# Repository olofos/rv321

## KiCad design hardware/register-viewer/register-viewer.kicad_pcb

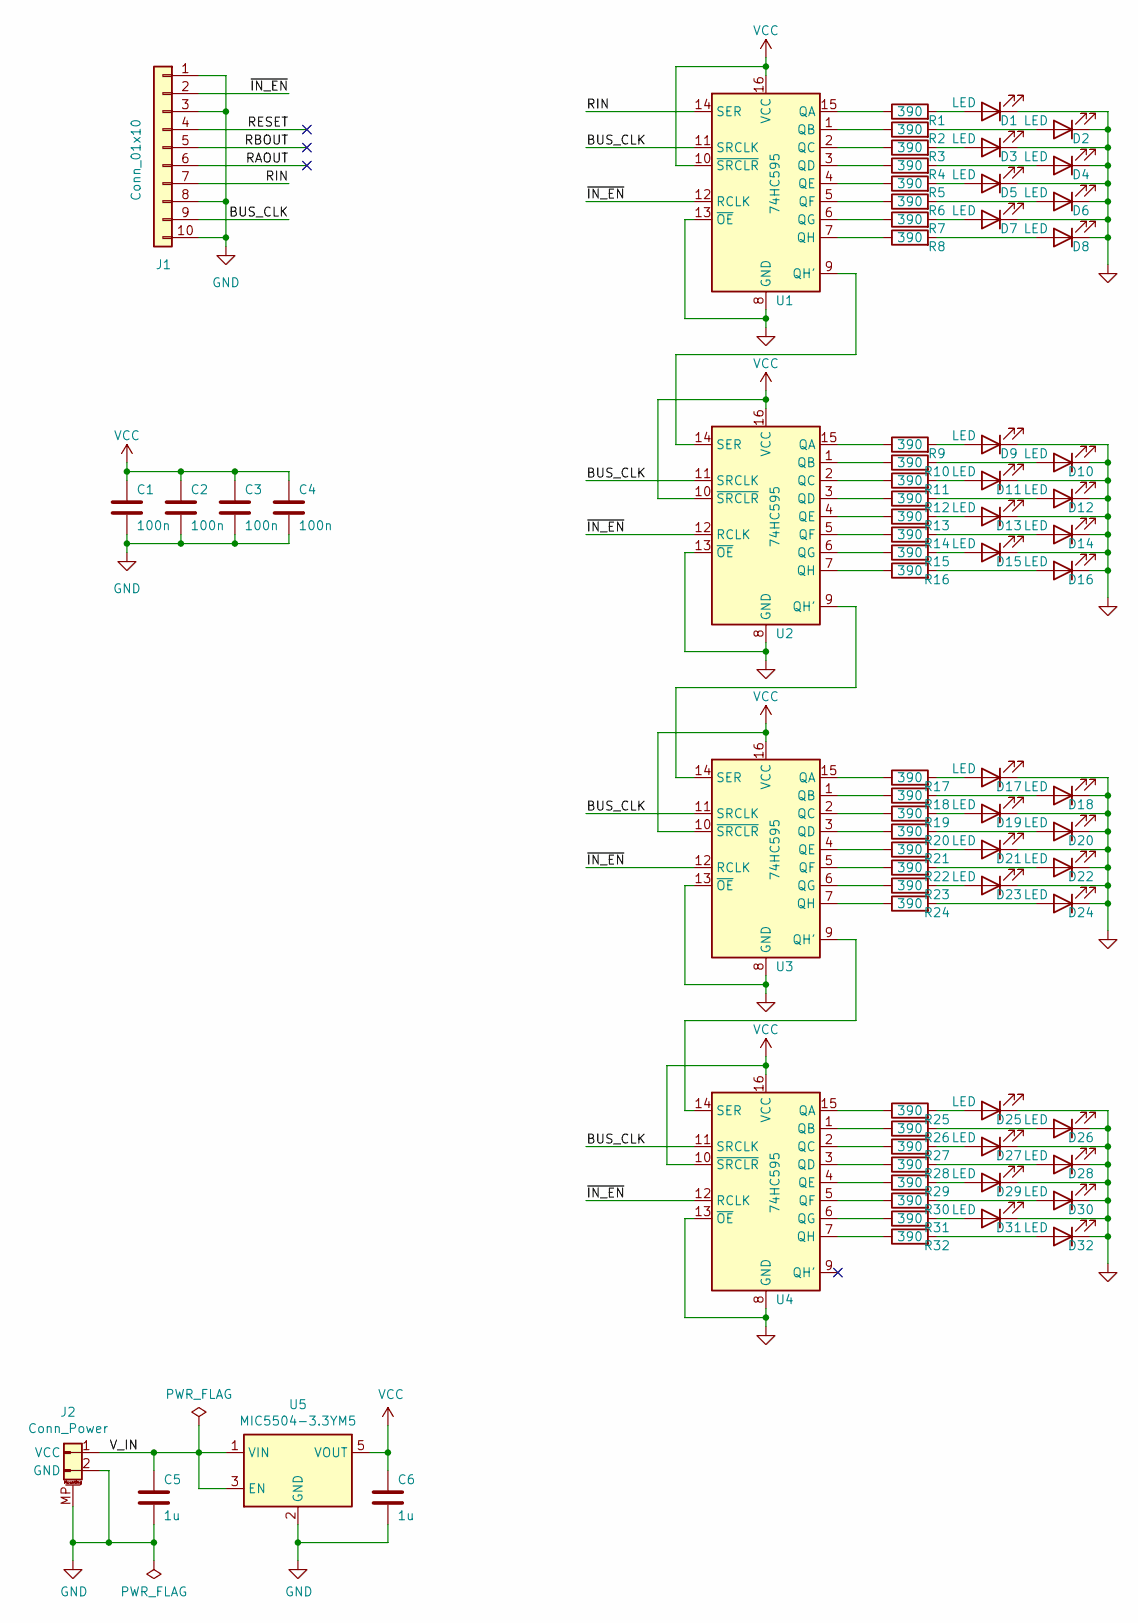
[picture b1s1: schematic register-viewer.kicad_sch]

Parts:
C1, C2, C3, C4: 100n; C_0805_2012Metric_Pad1.18x1.45mm_HandSolder
C5, C6: 1u; C_0805_2012Metric_Pad1.18x1.45mm_HandSolder
D1, D2, D3, D4, D5, D6, D7, D8, D9, D10, D11, D12, D13, D14, D15, D16, D17, D18, D19, D20, D21, D22, D23, D24, D25, D26, D27, D28, D29, D30, D31, D32: LED; LED_0805_2012Metric_Pad1.15x1.40mm_HandSolder
J1: Conn_01x10; IDC-Header_2x05_P2.54mm_Vertical
J2: Conn_Power; JST_PH_S2B-PH-SM4-TB_1x02-1MP_P2.00mm_Horizontal
R1, R2, R3, R4, R5, R6, R7, R8, R9, R10, R11, R12, R13, R14, R15, R16, R17, R18, R19, R20, R21, R22, R23, R24, R25, R26, R27, R28, R29, R30, R31, R32: 390; R_0805_2012Metric_Pad1.20x1.40mm_HandSolder
U1, U2, U3, U4: 74HC595; SOIC-16_3.9x9.9mm_P1.27mm
U5: MIC5504-3.3YM5; SOT-23-5_HandSoldering

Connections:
/BUS_CLK: J1.9, U1.11 (SRCLK), U2.11 (SRCLK), U3.11 (SRCLK), U4.11 (SRCLK)
/RAOUT: J1.6
/RBOUT: J1.5
/RESET: J1.4
/RIN: J1.7, U1.14 (SER)
/V_IN: C5.1, J2.1 (VCC), U5.1 (VIN), U5.3 (EN)
/~IN_EN: J1.2, U1.12 (RCLK), U2.12 (RCLK), U3.12 (RCLK), U4.12 (RCLK)
GND: C1.2, C2.2, C3.2, C4.2, C5.2, C6.2, D1.1 (K), D2.1 (K), D3.1 (K), D4.1 (K), D5.1 (K), D6.1 (K), D7.1 (K), D8.1 (K), D9.1 (K), D10.1 (K), D11.1 (K), D12.1 (K), D13.1 (K), D14.1 (K), D15.1 (K), D16.1 (K), D17.1 (K), D18.1 (K), D19.1 (K), D20.1 (K), D21.1 (K), D22.1 (K), D23.1 (K), D24.1 (K), D25.1 (K), D26.1 (K), D27.1 (K), D28.1 (K), D29.1 (K), D30.1 (K), D31.1 (K), D32.1 (K), J1.1, J1.3, J1.8, J1.10, J2.2 (GND), J2.MP, U1.8 (GND), U1.13 (~OE), U2.8 (GND), U2.13 (~OE), U3.8 (GND), U3.13 (~OE), U4.8 (GND), U4.13 (~OE), U5.2 (GND)
unnamed: D1.2 (A), R1.2
unnamed: D2.2 (A), R2.2
unnamed: D3.2 (A), R3.2
unnamed: D4.2 (A), R4.2
unnamed: D5.2 (A), R5.2
unnamed: D6.2 (A), R6.2
unnamed: D7.2 (A), R7.2
unnamed: D8.2 (A), R8.2
unnamed: D9.2 (A), R9.2
unnamed: D10.2 (A), R10.2
unnamed: D11.2 (A), R11.2
unnamed: D12.2 (A), R12.2
unnamed: D13.2 (A), R13.2
unnamed: D14.2 (A), R14.2
unnamed: D15.2 (A), R15.2
unnamed: D16.2 (A), R16.2
unnamed: D17.2 (A), R17.2
unnamed: D18.2 (A), R18.2
unnamed: D19.2 (A), R19.2
unnamed: D20.2 (A), R20.2
unnamed: D21.2 (A), R21.2
unnamed: D22.2 (A), R22.2
unnamed: D23.2 (A), R23.2
unnamed: D24.2 (A), R24.2
unnamed: D25.2 (A), R25.2
unnamed: D26.2 (A), R26.2
unnamed: D27.2 (A), R27.2
unnamed: D28.2 (A), R28.2
unnamed: D29.2 (A), R29.2
unnamed: D30.2 (A), R30.2
unnamed: D31.2 (A), R31.2
unnamed: D32.2 (A), R32.2
unnamed: R1.1, U1.15 (QA)
unnamed: R2.1, U1.1 (QB)
unnamed: R3.1, U1.2 (QC)
unnamed: R4.1, U1.3 (QD)
unnamed: R5.1, U1.4 (QE)
unnamed: R6.1, U1.5 (QF)
unnamed: R7.1, U1.6 (QG)
unnamed: R8.1, U1.7 (QH)
unnamed: R9.1, U2.15 (QA)
unnamed: R10.1, U2.1 (QB)
unnamed: R11.1, U2.2 (QC)
unnamed: R12.1, U2.3 (QD)
unnamed: R13.1, U2.4 (QE)
unnamed: R14.1, U2.5 (QF)
unnamed: R15.1, U2.6 (QG)
unnamed: R16.1, U2.7 (QH)
unnamed: R17.1, U3.15 (QA)
unnamed: R18.1, U3.1 (QB)
unnamed: R19.1, U3.2 (QC)
unnamed: R20.1, U3.3 (QD)
unnamed: R21.1, U3.4 (QE)
unnamed: R22.1, U3.5 (QF)
unnamed: R23.1, U3.6 (QG)
unnamed: R24.1, U3.7 (QH)
unnamed: R25.1, U4.15 (QA)
unnamed: R26.1, U4.1 (QB)
unnamed: R27.1, U4.2 (QC)
unnamed: R28.1, U4.3 (QD)
unnamed: R29.1, U4.4 (QE)
unnamed: R30.1, U4.5 (QF)
unnamed: R31.1, U4.6 (QG)
unnamed: R32.1, U4.7 (QH)
unnamed: U1.9 (QH'), U2.14 (SER)
unnamed: U2.9 (QH'), U3.14 (SER)
unnamed: U3.9 (QH'), U4.14 (SER)
VCC: C1.1, C2.1, C3.1, C4.1, C6.1, U1.10 (~SRCLR), U1.16 (VCC), U2.10 (~SRCLR), U2.16 (VCC), U3.10 (~SRCLR), U3.16 (VCC), U4.10 (~SRCLR), U4.16 (VCC), U5.5 (VOUT)

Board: 2 copper layers, 77 parts (0 on the bottom side), 73 nets, no tracks yet.

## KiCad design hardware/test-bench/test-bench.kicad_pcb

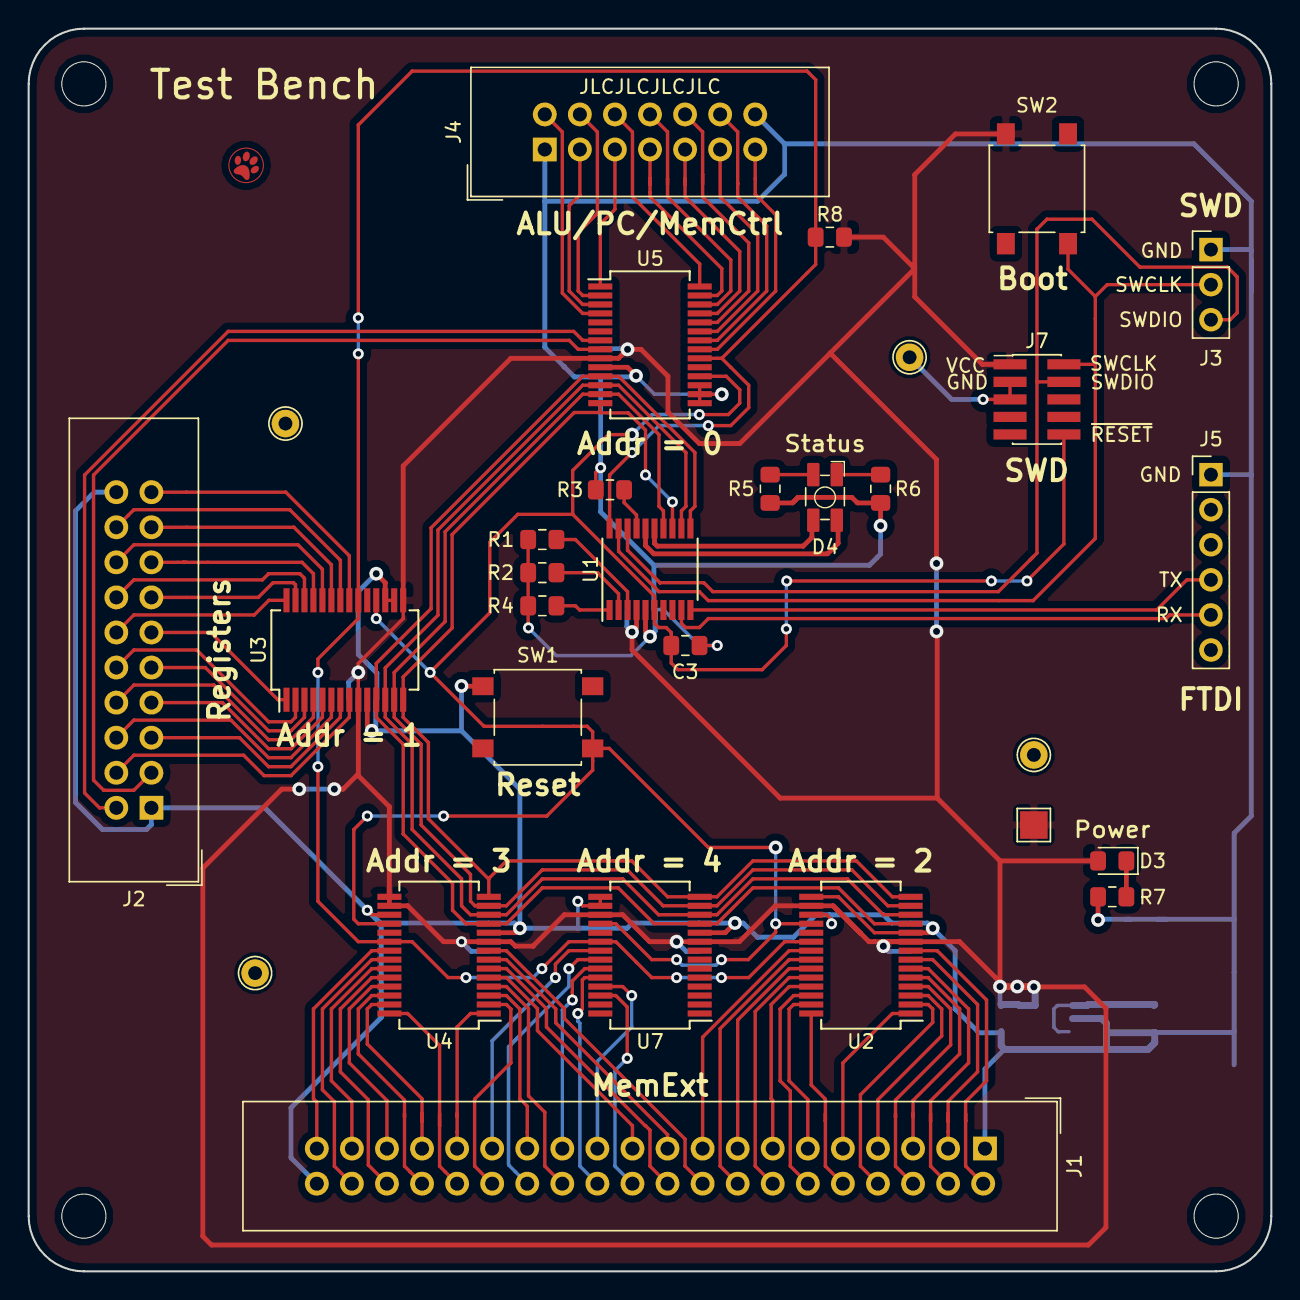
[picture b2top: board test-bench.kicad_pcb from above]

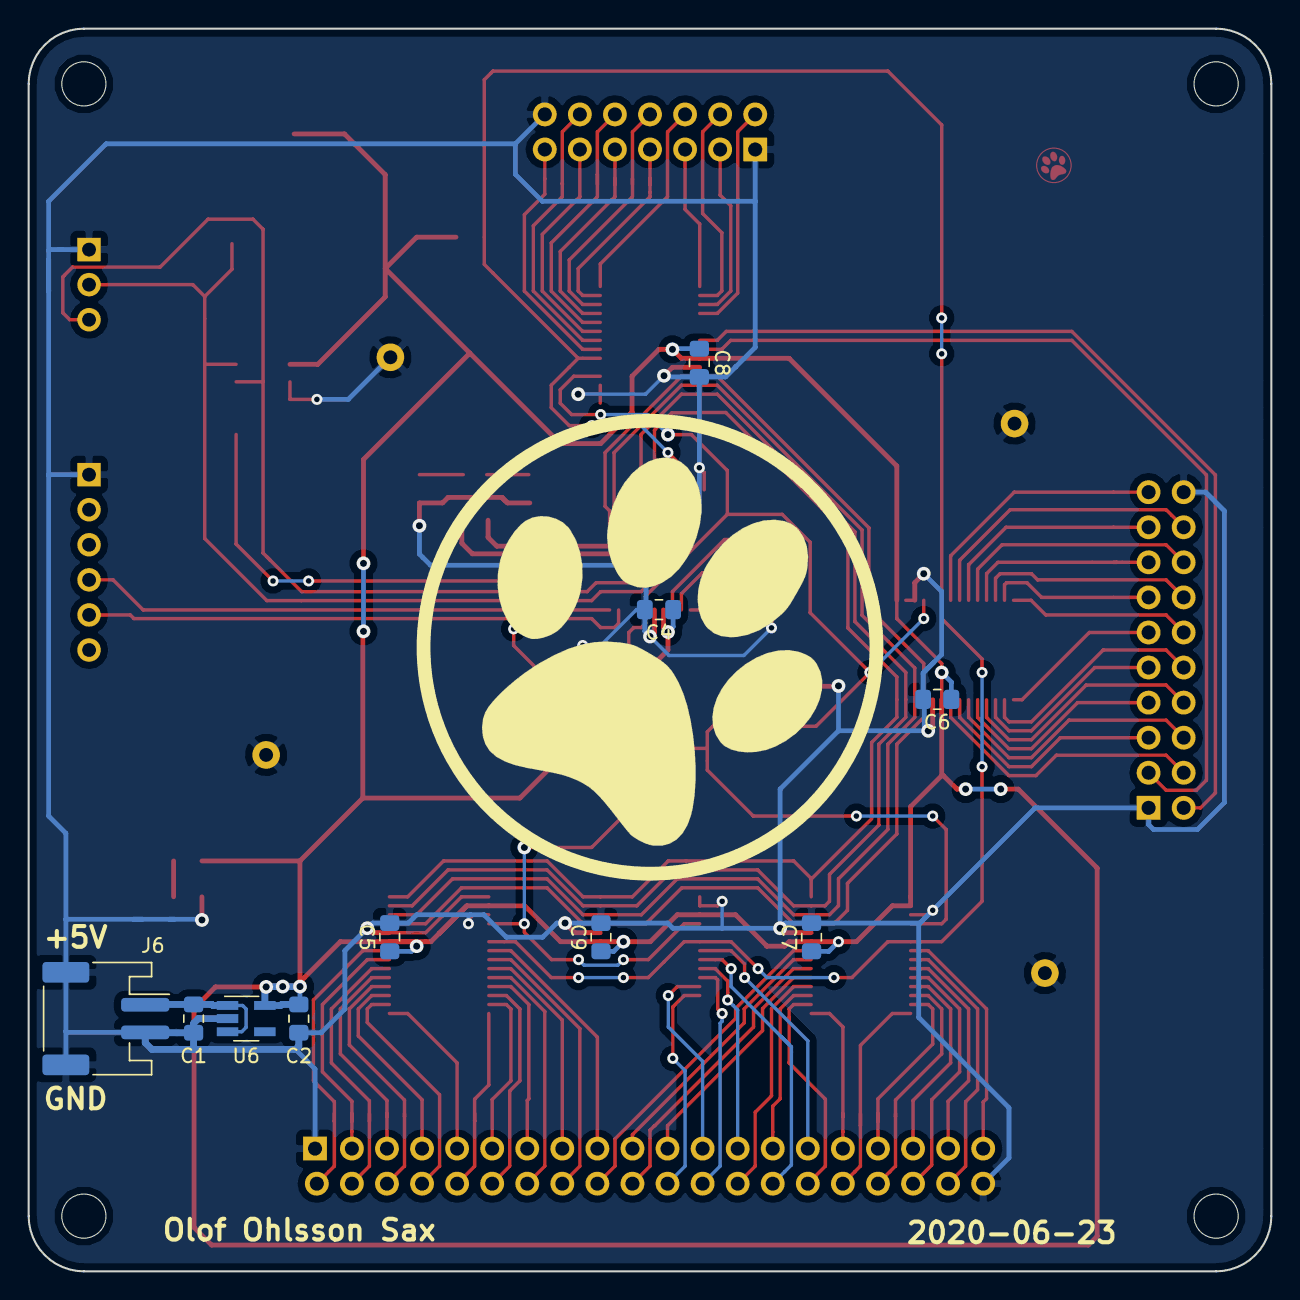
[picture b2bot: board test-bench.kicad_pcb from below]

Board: 2 copper layers, 90.0 x 90.0 mm, 44 parts (10 on the bottom side), 90 nets.

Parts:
C1, C2: 1u; C_0805_2012Metric_Pad1.15x1.40mm_HandSolder
C3, C4, C5, C6, C7, C8, C9: 100n; C_0805_2012Metric_Pad1.15x1.40mm_HandSolder
D3: Power; LED_0805_2012Metric_Pad1.15x1.40mm_HandSolder
D4: 150141RV73100; Wurth WL-SBTW
H1, H2, H3, H4: MountingHole; MountingHole_3.2mm_M3
J1: Conn_Mem_Ext; IDC-Header_2x20_P2.54mm_Vertical
J2: Conn_Reg; IDC-Header_2x10_P2.54mm_Vertical
J3: SWD; PinHeader_1x03_P2.54mm_Vertical
J4: Conn_Mem; IDC-Header_2x07_P2.54mm_Vertical
J5: FTDI; PinHeader_1x06_P2.54mm_Vertical
J6: Conn_Power; JST_PH_S2B-PH-SM4-TB_1x02-1MP_P2.00mm_Horizontal
J7: J_LINK_SWD; PinHeader_2x05_P1.27mm_Vertical_SMD
R1, R2, R3, R4, R8: 10k; R_0805_2012Metric_Pad1.15x1.40mm_HandSolder
R5, R6: 220; R_0805_2012Metric_Pad1.15x1.40mm_HandSolder
R7: 330; R_0805_2012Metric_Pad1.15x1.40mm_HandSolder
SW1, SW2: SW_Push_4pin; SW_SPST_DTSM-6
TP1, TP2, TP3, TP4: TestPoint; TestPoint_THTPad_D2.0mm_Drill1.0mm
TP5: TestPoint; TestPoint_Pad_2.0x2.0mm
U1: STM32G030F6; TSSOP-20_4.4x6.5mm_P0.65mm
U2, U3, U4, U5, U7: MCP23S17_SS; SSOP-28_5.3x10.2mm_P0.65mm
U6: MIC5504-3.3YM5; SOT-23-5_HandSoldering

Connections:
/FTDI_RX: J5.5, U1.9
/FTDI_TX: J5.4, U1.10
/GREEN: D4.2, U1.15
/INT: R8.1, U1.20, U2.20, U3.20, U4.20, U5.20, U7.20
/IO0A0: J4.13, U5.21
/IO0A1: J4.12, U5.22
/IO0A2: J4.11, U5.23
/IO0A3: J4.10, U5.24
/IO0A4: J4.9, U5.25
/IO0A5: J4.8, U5.26
/IO0A6: J4.7, U5.27
/IO0A7: J4.6, U5.28
/IO0B0: J4.5, U5.1
/IO0B1: J4.4, U5.2
/IO0B2: J4.3, U5.3
/IO0B3: J4.2, U5.4
/IO0B6: J2.2, U5.7
/IO0B7: J2.3, U5.8
/IO1A0: J2.19, U3.21
/IO1A1: J2.18, U3.22
/IO1A2: J2.17, U3.23
/IO1A3: J2.16, U3.24
/IO1A4: J2.15, U3.25
/IO1A5: J2.14, U3.26
/IO1A6: J2.13, U3.27
/IO1A7: J2.12, U3.28
/IO1B0: J2.11, U3.1
/IO1B1: J2.10, U3.2
/IO1B2: J2.9, U3.3
/IO1B3: J2.8, U3.4
/IO1B4: J2.7, U3.5
/IO1B5: J2.6, U3.6
/IO1B6: J2.5, U3.7
/IO1B7: J2.4, U3.8
/IO2A0: J1.17, U2.21
/IO2A1: J1.16, U2.22
/IO2A2: J1.15, U2.23
/IO2A3: J1.14, U2.24
/IO2A4: J1.13, U2.25
/IO2A5: J1.12, U2.26
/IO2A6: J1.11, U2.27
/IO2A7: J1.10, U2.28
/IO2B0: J1.9, U2.1
/IO2B1: J1.8, U2.2
/IO2B2: J1.7, U2.3
/IO2B3: J1.6, U2.4
/IO2B4: J1.5, U2.5
/IO2B5: J1.4, U2.6
/IO2B6: J1.3, U2.7
/IO2B7: J1.2, U2.8
/IO3A0: J1.39, U4.21
/IO3A1: J1.38, U4.22
/IO3A2: J1.37, U4.23
/IO3A3: J1.36, U4.24
/IO3A4: J1.35, U4.25
/IO3A5: J1.34, U4.26
/IO3A6: J1.33, U4.27
/IO3A7: J1.32, U4.28
/IO3B0: J1.31, U4.1
/IO3B1: J1.30, U4.2
/IO3B2: J1.27, U4.3
/IO3B3: J1.26, U4.4
/IO3B4: J1.21, U4.5
/IO3B5: J1.20, U4.6
/IO3B6: J1.19, U4.7
/IO3B7: J1.18, U4.8
/IO4A0: J1.29, U7.21
/IO4A1: J1.28, U7.22
/IO4A2: J1.25, U7.23
/IO4A3: J1.24, U7.24
/IO4A4: J1.23, U7.25
/IO4A5: J1.22, U7.26
/LED_G_K: D4.4, R5.2
/LED_POWER_K: D3.1, R7.2
/LED_R_K: D4.3, R6.2
/MISO: U1.13, U2.14, U3.14, U4.14, U5.14, U7.14
/MOSI: U1.14, U2.13, U3.13, U4.13, U5.13, U7.13
/PA14: R3.2, U1.17
/PB7: R4.2, U1.1
/PC14: R2.2, U1.2
/PC15: R1.2, U1.3
/RED: D4.1, U1.16
/SCK: U1.12, U2.12, U3.12, U4.12, U5.12, U7.12
/SWCLK: J3.2, J7.2, SW2.3, U1.19
/SWDIO: J3.3, J7.4, U1.18
/V_IN: C1.1, J6.1, U6.1, U6.3
/~CS: U1.11, U2.11, U3.11, U4.11, U5.11, U7.11
/~RESET: C3.1, J7.10, SW1.4, U1.6, U2.18, U3.18, U4.18, U5.18, U7.18
GND: C1.2, C2.2, C3.2, C4.2, C5.2, C6.2, C7.2, C8.2, C9.2, J1.1, J1.40, J2.1, J2.20, J3.1, J4.1, J4.14, J5.1, J6.2, J6.MP, J7.3, J7.5, R1.1, R2.1, R3.1, R4.1, R5.1, R6.1, R7.1, SW1.1, TP1.1, TP2.1, TP3.1, TP4.1, U1.5, U2.10, U2.15, U2.17, U3.10, U3.16, U3.17, U4.10, U4.17, U5.10, U5.15, U5.16, U5.17, U6.2, U7.10, U7.15, U7.16
VCC: C2.1, C4.1, C5.1, C6.1, C7.1, C8.1, C9.1, D3.2, J7.1, R8.2, SW2.2, TP5.1, U1.4, U2.9, U2.16, U3.9, U3.15, U4.9, U4.15, U4.16, U5.9, U6.5, U7.9, U7.17
